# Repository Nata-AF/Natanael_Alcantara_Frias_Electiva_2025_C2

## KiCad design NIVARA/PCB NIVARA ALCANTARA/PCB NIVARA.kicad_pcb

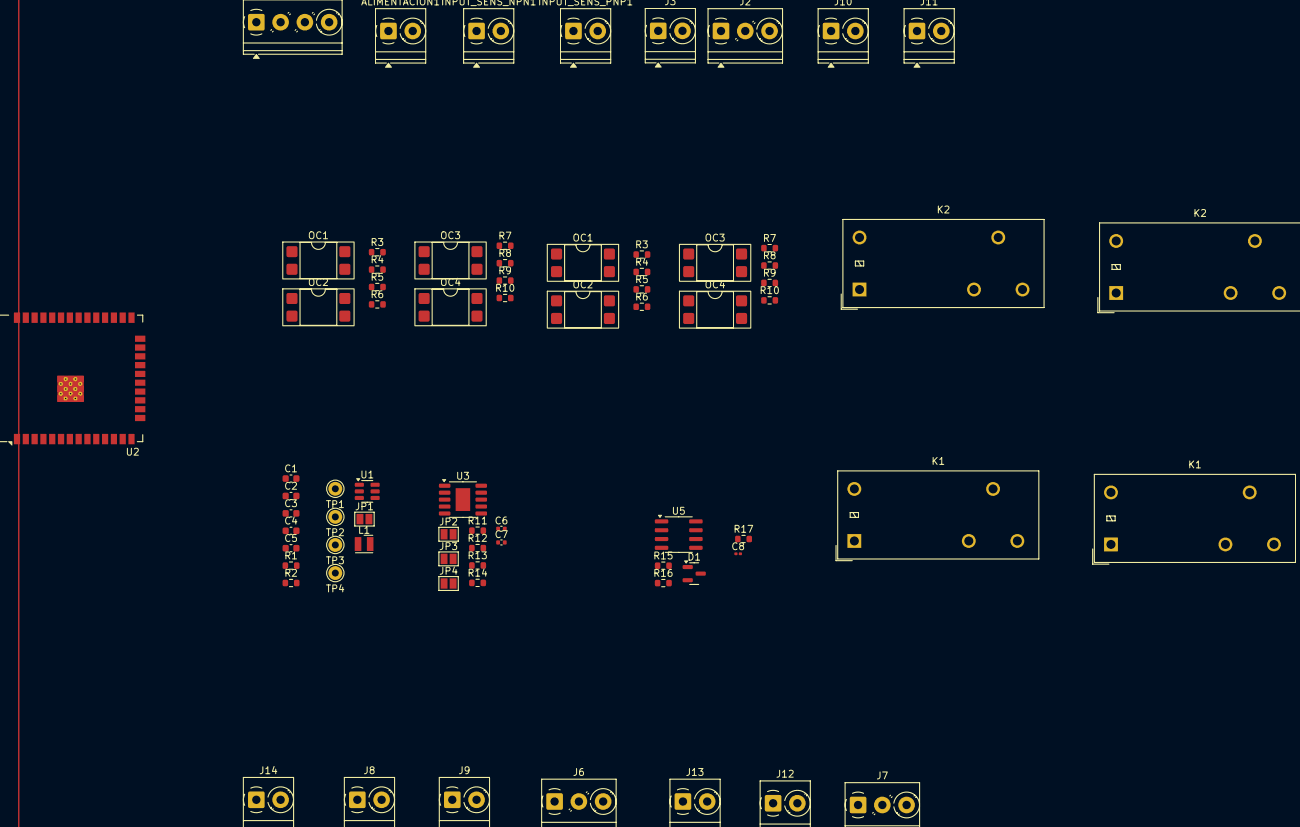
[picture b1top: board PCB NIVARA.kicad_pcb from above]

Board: 2 copper layers, 74 parts (0 on the bottom side), 35 nets, no tracks yet.

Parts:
ALIMENTACION1: 5-24V; TerminalBlock_Phoenix_PT-1,5-2-3.5-H_1x02_P3.50mm_Horizontal
C1: 10uF; C_0603_1608Metric
C2: 100nF; C_0603_1608Metric
C3: 10pF; C_0603_1608Metric
C4, C5: 22uF; C_0603_1608Metric
C6: 220pF; C_0402_1005Metric
C7: 1uF; C_0402_1005Metric
C8: 100nF; C_0201_0603Metric
D1: SM712_SOT23; SOT-23
INPUT_SENS_NPN1: TerminalBlock_Phoenix_PT-1,5-2-3.5-H_1x02_P3.50mm_Horizontal
INPUT_SENS_PNP1: TerminalBlock_Phoenix_PT-1,5-2-3.5-H_1x02_P3.50mm_Horizontal
J2: RS485; TerminalBlock_Phoenix_PT-1,5-3-3.5-H_1x03_P3.50mm_Horizontal
J3, J10: ENTRADA 0-32; TerminalBlock_Phoenix_PT-1,5-2-3.5-H_1x02_P3.50mm_Horizontal
J6, J7: relay1 out; TerminalBlock_Phoenix_PT-1,5-3-3.5-H_1x03_P3.50mm_Horizontal
J8: Salida npn; TerminalBlock_Phoenix_PT-1,5-2-3.5-H_1x02_P3.50mm_Horizontal
J9: Salida pnp; TerminalBlock_Phoenix_PT-1,5-2-3.5-H_1x02_P3.50mm_Horizontal
J11: 4-20mA; TerminalBlock_Phoenix_PT-1,5-2-3.5-H_1x02_P3.50mm_Horizontal
J12: salida 0-10; TerminalBlock_Phoenix_PT-1,5-2-3.5-H_1x02_P3.50mm_Horizontal
J13: salida 0-32; TerminalBlock_Phoenix_PT-1,5-2-3.5-H_1x02_P3.50mm_Horizontal
J14: salida 4-20mA; TerminalBlock_Phoenix_PT-1,5-2-3.5-H_1x02_P3.50mm_Horizontal
J15: INTERRUPTOR; TerminalBlock_Phoenix_PT-1,5-4-3.5-H_1x04_P3.50mm_Horizontal
JP1, JP2, JP3, JP4: SolderJumper_2_Open; SolderJumper-2_P1.3mm_Open_Pad1.0x1.5mm
K1, K1#2, K2, K2#2: G2RL-1; Relay_SPDT_Omron_G2RL-1
L1: L_Iron; L_Wurth_WE-LQSH-2512
OC1, OC1#2, OC2, OC2#2, OC3, OC3#2, OC4, OC4#2: PC817; DIP-4_W7.62mm_SMDSocket_SmallPads
R1, R2: 22k; R_0603_1608Metric
R3, R3#2, R4, R4#2, R7, R7#2, R8, R8#2: 1K; R_0603_1608Metric
R5, R5#2, R6, R6#2, R9, R9#2, R10, R10#2: 550; R_0603_1608Metric
R11, R12, R13: 10k; R_0603_1608Metric
R14: 2.5k; R_0603_1608Metric
R15, R16, R17: 10K; R_0603_1608Metric
TP1, TP2, TP3, TP4: TestPoint; Pin_D1.0mm_L10.0mm
U1: AP63203WU; TSOT-23-6
U2: ESP32-WROOM-32D
U3: SSOP-10-1EP_3.9x4.9mm_P1mm_EP2.1x3.3mm
U5: SP3485EN; SOIC-8_3.9x4.9mm_P1.27mm

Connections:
+3.3V: C8.2, JP1.1 (A), R5.2, R5#2.2, R6.2, R6#2.2, R9.2, R9#2.2, R10.2, R10#2.2, R15.2, TP4.1, U5.8 (VCC)
/BOARD/E-NPN 0: INPUT_SENS_NPN1.1, R3.1, R3#2.1
/BOARD/E-NPN 1: INPUT_SENS_NPN1.2, R4.1, R4#2.1
/BOARD/E-PNP 0: INPUT_SENS_PNP1.1, R7.1, R7#2.1
/BOARD/E-PNP 1: INPUT_SENS_PNP1.2, R8.1, R8#2.1
/BOARD/RELAY/ACT_RELAY1: K1.A2, K1#2.A2
/BOARD/RELAY/ACT_RELAY2: K2.A2, K2#2.A2
/BOARD/RELAY/RELAY1 COS: K1.11, K1#2.11
/BOARD/RELAY/RELAY1 NA: K1.14, K1#2.14
/BOARD/RELAY/RELAY1 NC: K1.12, K1#2.12
/BOARD/RELAY/RELAY2 COS: K2.11, K2#2.11
/BOARD/RELAY/RELAY2 NA: K2.14, K2#2.14
/BOARD/RELAY/RELAY2 NC: K2.12, K2#2.12
/BOARD/RS485/RS-485 A: D1.2 (A2), R15.1, R16.2, U5.6 (A)
/BOARD/RS485/RS-485 B: D1.1 (A1), R16.1, R17.2, U5.7 (B)
/BOARD/RS485/~TX/RX: U5.2 (~RE), U5.3 (DE)
/BOARD/S-NPN 0: J8.1, OC1.4, OC1#2.4, R5.1, R5#2.1
/BOARD/S-NPN 1: J8.2, OC2.4, OC2#2.4, R6.1, R6#2.1
/BOARD/S-PNP 0: J9.1, OC3.4, OC3#2.4, R9.1, R9#2.1
/BOARD/S-PNP 1: J9.2, OC4.4, OC4#2.4, R10.1, R10#2.1
GND: ALIMENTACION1.2, C1.2, C4.1, C5.1, C6.2, C7.2, C8.1, D1.3 (common), J2.3, J3.2, J10.2, J11.2, J12.2, J13.2, J14.2, J15.4, JP2.1 (A), JP3.1 (A), JP4.1 (A), OC1.2, OC1.3, OC1#2.2, OC1#2.3, OC2.2, OC2.3, OC2#2.2, OC2#2.3, OC3.2, OC3.3, OC3#2.2, OC3#2.3, OC4.2, OC4.3, OC4#2.2, OC4#2.3, R2.1, R14.2, R17.1, U1.4 (GND), U2.1 (GND), U2.15 (GND), U2.38 (GND), U2.39 (GND), U3.6 (GND), U5.5 (GND)
unnamed: C3.2, C4.2, C5.2, JP1.2 (B), L1.2, R1.2, TP2.1
unnamed: JP2.2 (B), R11.2, U3.9 (A2)
unnamed: JP3.2 (B), R12.2, U3.4 (A1)
unnamed: JP4.2 (B), R13.2, U3.3 (A0)
unnamed: OC1.1, OC1#2.1, R3.2, R3#2.2
unnamed: OC2.1, OC2#2.1, R4.2, R4#2.2
unnamed: OC3.1, OC3#2.1, R7.2, R7#2.2
unnamed: OC4.1, OC4#2.1, R8.2, R8#2.2
unnamed: C2.1, U1.6 (BST)
unnamed: C3.1, R1.1, R2.2, TP1.1, U1.1 (FB)
unnamed: C2.2, L1.1, U1.5 (SW)
unnamed: C6.1, R14.1, U3.7 (SET)
unnamed: C7.1, R11.1, R12.1, R13.1, U3.10 (V5V)
VCC: ALIMENTACION1.1, C1.1, K1.A1, K1#2.A1, K2.A1, K2#2.A1, TP3.1, U1.2 (EN), U1.3 (IN), U3.5 (VCC)

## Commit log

2025-08-15 Esquema/Entradas An.Dig
2025-08-15 NIVARA/PCB
2025-08-15 Add files via upload
    Garabato
2025-08-22 Tarea 1
    Ingeniería de los Requerimientos
2025-08-22 Tarea 1
